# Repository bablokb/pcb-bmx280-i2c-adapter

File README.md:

An Adapter PCB for BME280/BMP280 Breakouts Supporting Stemma/Qt and Grove
=========================================================================

Here are the KiCAD (v7) design-files for a small adapter PCB adding
Stemma/Qt and/or Grove I2C-connectors to a BME280/BMP280 breakout. These
breakouts are omnipresent under names like GY-BME280/GY-BMP280. Be
careful, both breakouts look identical and some sellers cheat you: they
send the cheaper BMP280-variant instead of the BME280-variant.

The breakout suports two Stemma/Qt on top and bottom. On the top
side, you can also add two horizontal Grove-connectors. For the
bottom side, only vertical Grove-connectors will work.

The directory `3D` contains design-files for an enclosure in OpenSCAD format.
You also need the [BOSL2-Library](https://github.com/BelfrySCAD/BOSL2).

Schematic
---------

Layout
------

3D-Views
--------

License
-------

[![CC BY-SA 4.0][cc-by-sa-shield]][cc-by-sa]

This work is licensed under a
[Creative Commons Attribution-ShareAlike 4.0 International
License][cc-by-sa].

[![CC BY-SA 4.0][cc-by-sa-image]][cc-by-sa]

[cc-by-sa]: http://creativecommons.org/licenses/by-sa/4.0/
[cc-by-sa-image]: https://licensebuttons.net/l/by-sa/4.0/88x31.png
[cc-by-sa-shield]:
https://img.shields.io/badge/License-CC%20BY--SA%204.0-lightgrey.svg

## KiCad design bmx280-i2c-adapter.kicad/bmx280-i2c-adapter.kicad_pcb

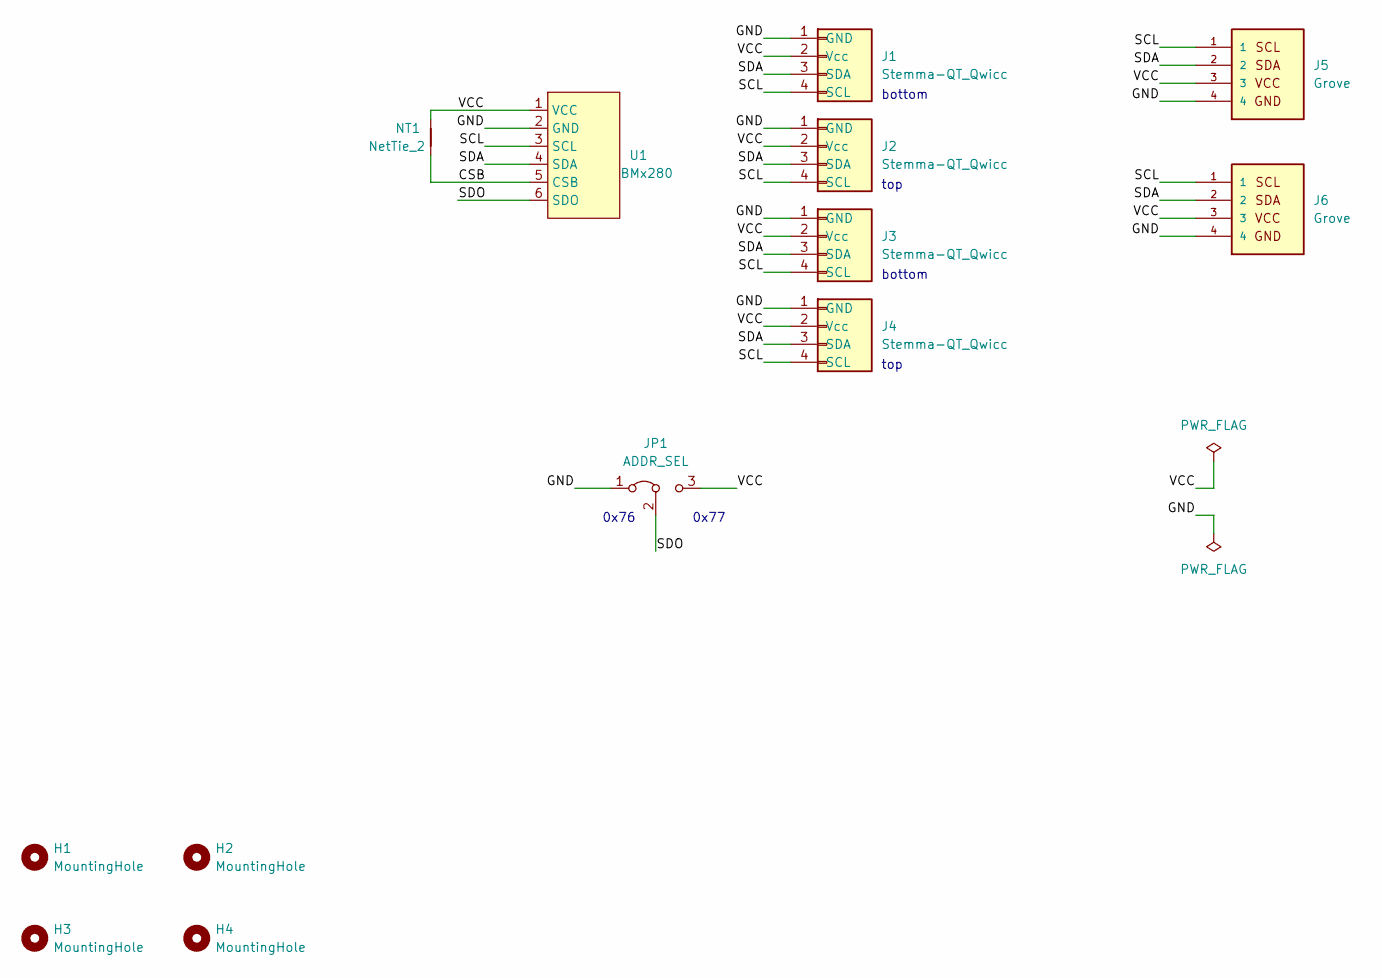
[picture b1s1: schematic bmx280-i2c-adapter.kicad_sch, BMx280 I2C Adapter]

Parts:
H1, H2, H3, H4: MountingHole; MountingHole_3mm
J1, J2, J3, J4: Stemma-QT_Qwicc; JST_SH_SM04B-SRSS-TB_1x04-1MP_P1.00mm_Horizontal; LCSC C160404
J5, J6: Grove; grove_horizontal
JP1: ADDR_SEL; SolderJumper-3_P1.3mm_Bridged12_Pad1.0x1.5mm
NT1: NetTie_2; NetTie-2_SMD_Pad0.5mm
U1: BMx280; BMx280_Breakout

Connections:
/CSB: NT1.1, U1.5 (CSB)
/GND: J1.1 (GND), J2.1 (GND), J3.1 (GND), J4.1 (GND), J5.4, J6.4, JP1.1 (A), U1.2 (GND)
/SCL: J1.4 (SCL), J2.4 (SCL), J3.4 (SCL), J4.4 (SCL), J5.1, J6.1, U1.3 (SCL)
/SDA: J1.3 (SDA), J2.3 (SDA), J3.3 (SDA), J4.3 (SDA), J5.2, J6.2, U1.4 (SDA)
/SDO: JP1.2 (C), U1.6 (SDO)
/VCC: J1.2 (Vcc), J2.2 (Vcc), J3.2 (Vcc), J4.2 (Vcc), J5.3, J6.3, JP1.3 (B), NT1.2, U1.1 (VCC)

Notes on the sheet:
0x77
top
bottom
0x76

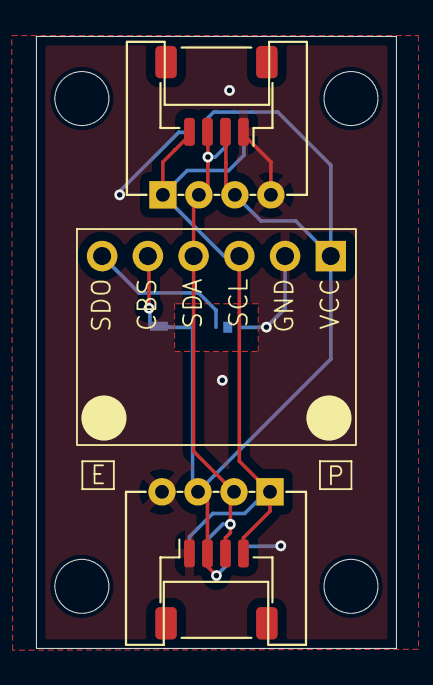
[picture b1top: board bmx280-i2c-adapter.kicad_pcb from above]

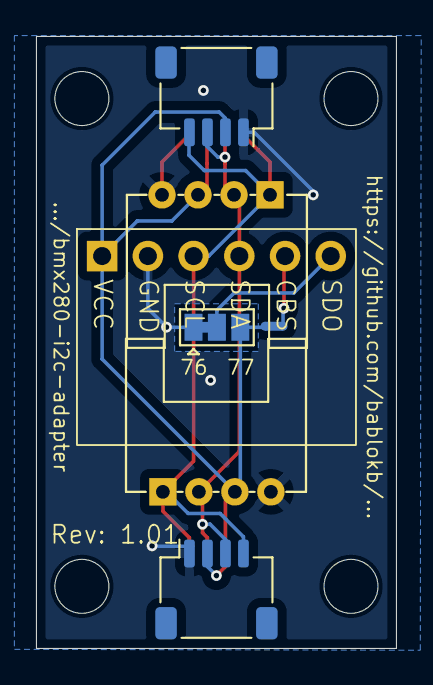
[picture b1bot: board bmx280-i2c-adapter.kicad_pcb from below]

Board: 2 copper layers, 20.0 x 34.0 mm, 13 parts (4 on the bottom side), 6 nets.

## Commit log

2024-08-01 added content
2024-08-01 fix spelling
2024-08-10 added generated 3D files
2024-08-10 first iteration of enclosure
2024-08-10 second iteration: add screw-hole and walls around Stemma; fix top-height
2024-08-20 add some depth to Stemma/Qt cutout
2024-08-23 added note about enclosure
2024-08-23 Rev 1.01: add assembly for Stemma/Qt on top side
